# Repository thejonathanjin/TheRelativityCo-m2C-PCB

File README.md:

# m2C: Mobile to Car Communication Module w/ AndroidOS (iOS TBD)

m2C is a capstone project among 4 students from San Jose State University.

The team aimed to achieve connectivity between an Android (and iOS TBD) mobile device and an automobile.

Successfully installed a prototype version in April 2014 in Hayward, Fremont, Milpitas, and San Jose California.

Currently, the lead competitor is Viper SmartStart.

## Installation

Download the latest Diptrace *.dch Schematic and *.dip PCB Layout files.

Tree:

```
.
├── Diptrace
│   └── *.dch
    └── *.dip
```

## Usage

*.dch

```python
```

*.dip

```python
```

KiCAD PCB project from converted DipTrace PCB Layout:

## Contributing

Pull requests are welcome. For major changes, please open an issue first
to discuss what you would like to change.

Please make sure to update tests as appropriate.

A major thanks to:

- Boran "Brian" Peng, Automotive Master Technician
- Shavinda De Silva, Communication Networks, SIM & GPS
- Joseph Nico Tankeh, Embedded Systems, Arduino & C++
- Jonathan Tuan Tran, Android & (iOS TBD)

... for initiating this project!

A big THANK YOU to Dr. David Parent.

## License

Creative Commons

[The Unlicense] (https://choosealicense.com/licenses/unlicense/)

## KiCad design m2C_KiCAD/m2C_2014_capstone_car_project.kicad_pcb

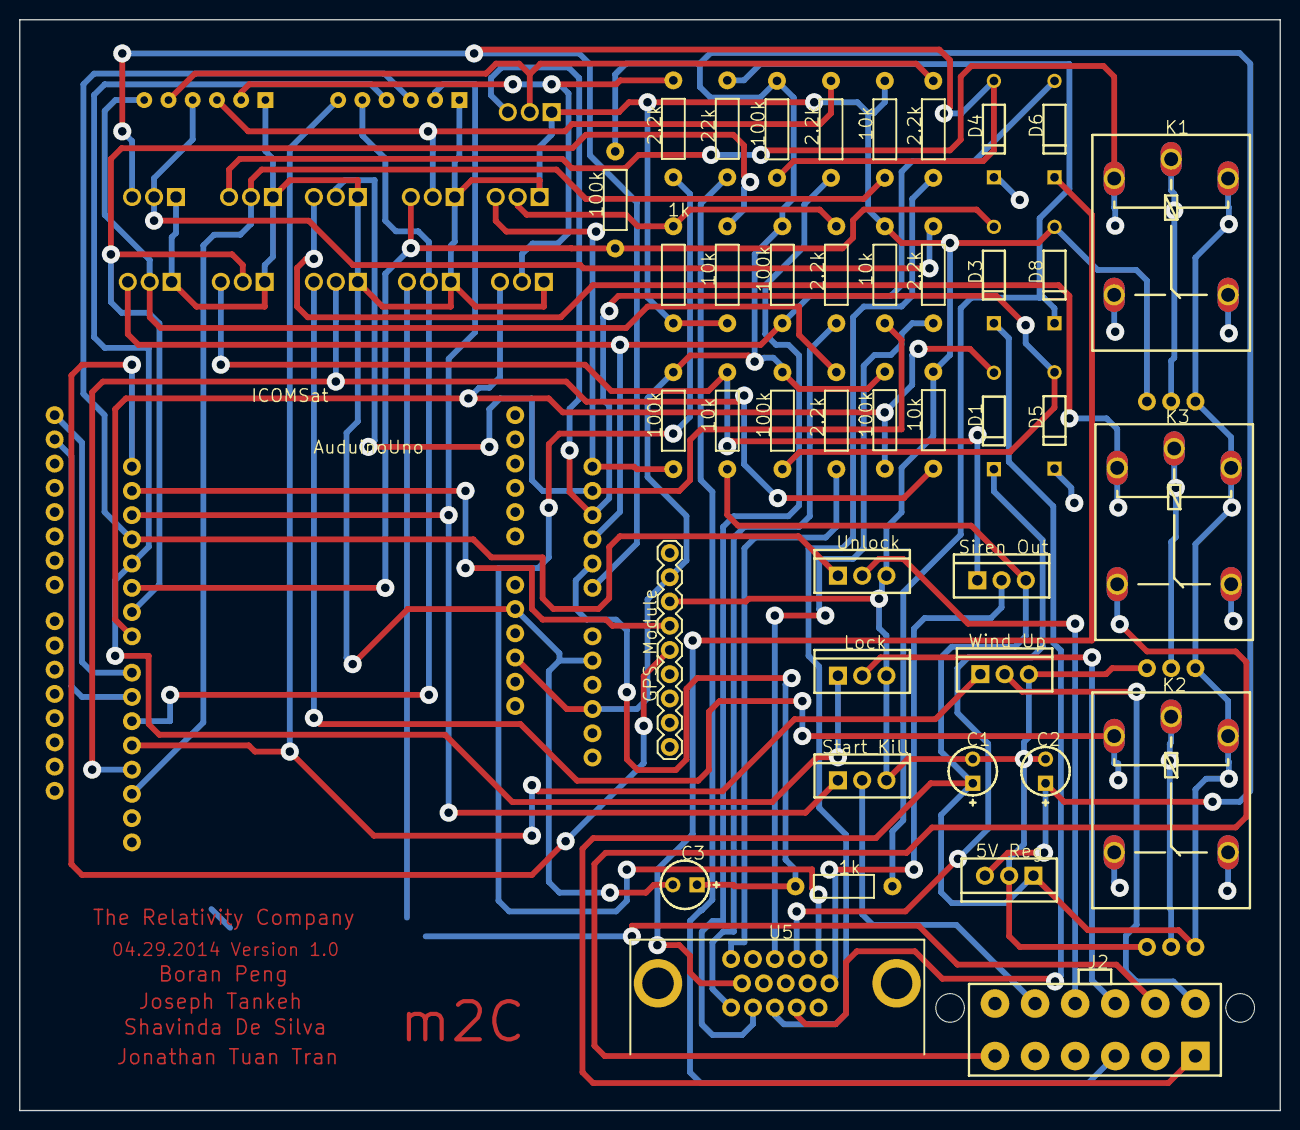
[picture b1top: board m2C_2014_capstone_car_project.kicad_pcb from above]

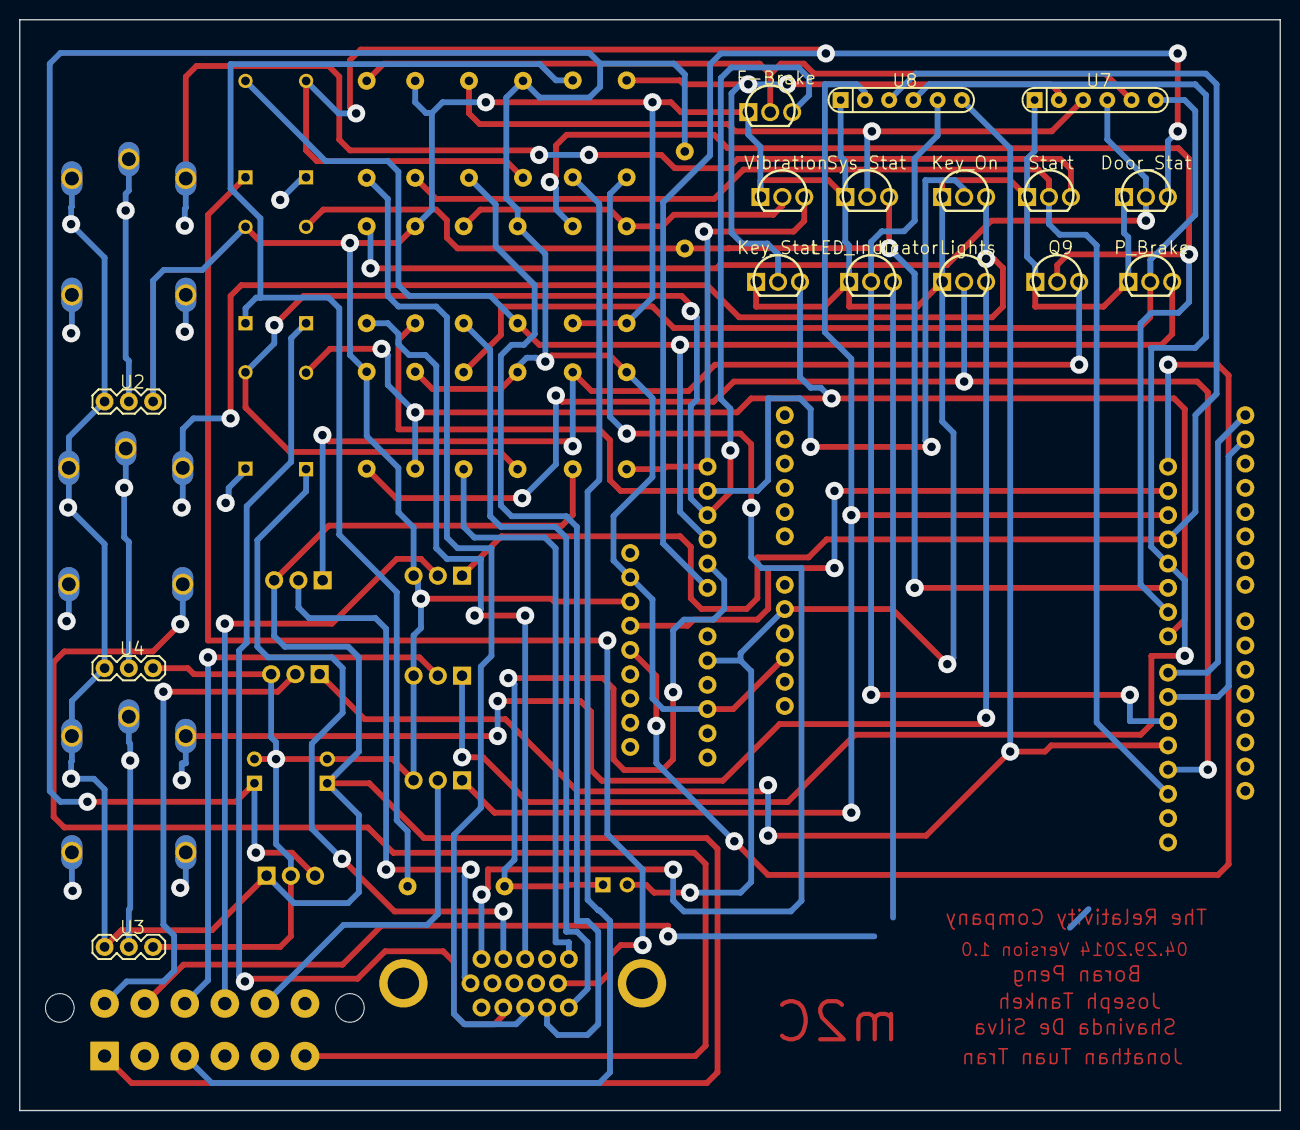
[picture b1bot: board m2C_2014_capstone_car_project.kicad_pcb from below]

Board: 2 copper layers, 132.1 x 114.3 mm, 59 parts (16 on the bottom side), 58 nets.

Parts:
AuduinoUno0: ARDUINO_SHIELDNO_SILK; DUEMILANOVE_VIAS
C1, C2: POLCAP; CAPPR-2.54_5.08
C3: POLCAP; CAPPR-2.54_5.08_C3
D1, D3, D4, D5, D6, D8: 1N4148; DO-35
Door_Stat0: 2N7000_B; TO-92_B
F-Brake0: 2N7000_B; TO-92_B
GPS_Module0: M09; 1X09
ICOMSat0: ARDUINO_SHIELDNO_SILK; DUEMILANOVE_VIAS
J2: 39-29-9123
K1, K2, K3: G5L; G5LE
Key_On0: 2N7000_B; TO-92_B
Key_Stat0: 2N7000_B; TO-92_B
LED_Indicator0: 2N7000_B; TO-92_B
Lights0: 2N7000_B; TO-92_B
Lock0: IRF641; TO-220_Lock
P_Brake0: 2N7000_B; TO-92_B
Q9: 2N7000_B; TO-92_B
R1: 1k; AXIAL-0.4
R3, R4, R5, R6, R7, R10: 100k; AXIAL-0.4_R3
R14: 1k; AXIAL-0.4_R14
R15, R17, R18, R19, R20, R21: 2.2k; AXIAL-0.4_R3
R22, R23, R25, R26, R27: 10k; AXIAL-0.4_R3
R24: 22k; AXIAL-0.4_R3
Siren_Out0: IRF9511; TO-220_Lock
Start0: 2N7000_B; TO-92_B
Start_Kill0: IRF641; TO-220_Lock
Sys_Stat0: 2N7000_B; TO-92_B
U2, U3, U4: JUMPER-3-OLDPTH; 1X03
U5: DB15
U7: 1k; RPACK-SIP-PTH-5
U8: 10k; RPACK-SIP-PTH-5
UNK5V_Reg0: MC7805ACT; TO-220
Unlock0: IRF641; TO-220_Lock
Vibration0: 2N7000_B; TO-92_B
Wind_Up0: IRF641; TO-220_Lock

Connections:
Net_0: AuduinoUno0.GND@1, C1.2, C2.2, C3.2, D8.2, Door_Stat0.1, F-Brake0.1, GPS_Module0.7, ICOMSat0.GND@1, J2.2, Key_On0.1, Key_Stat0.1, LED_Indicator0.1, Lights0.1, Lock0.3, P_Brake0.1, Q9.1, R14.P$1, R23.P$1, R25.P$2, R26.P$2, R27.P$2, Start0.1, Start_Kill0.3, Sys_Stat0.1, U2.1, U3.1, U4.1, U7.P$1, U8.P$1, UNK5V_Reg0.2, Unlock0.3, Vibration0.1, Wind_Up0.3
Net_1: AuduinoUno0.5V, C2.1, GPS_Module0.8, ICOMSat0.5V, R3.P$2, R4.P$2, R5.P$2, R6.P$2, R7.P$2, R10.P$2, UNK5V_Reg0.3
Net_2: R15.P$1, U5.1
Net_3: D1.1, U5.2
Net_4: R18.P$1, U5.3
Net_5: R20.P$1, U5.5
Net_6: AuduinoUno0.D6, Q9.2, R23.P$2
Net_7: C1.1, J2.1, K1.2, K2.2, K3.2, R22.P$1, Siren_Out0.3, U2.3, U3.3, U4.3, UNK5V_Reg0.1
Net_8: Siren_Out0.2, U5.6
Net_9: D4.1, U5.8
Net_10: D5.1, U5.9
Net_11: D6.1, U5.10
Net_12: D3.1, U5.12
Net_13: R19.P$1, U5.13
Net_14: R17.P$1, U5.14
Net_15: R21.P$1, U5.15
Net_16: J2.10, Unlock0.2
Net_17: AuduinoUno0.D11, U8.P$6, Wind_Up0.1
Net_18: J2.3, R24.P$1
Net_19: K2.P, U3.2
Net_20: AuduinoUno0.A4, Key_On0.2, R25.P$1
Net_21: AuduinoUno0.D13, R27.P$1, Start0.2
Net_22: AuduinoUno0.D12, Lights0.2, R26.P$1
Net_23: K2.1, Lights0.3
Net_24: K3.1, Key_On0.3
Net_25: K1.1, Start0.3
Net_26: F-Brake0.2, R19.P$2, U7.P$5
Net_27: P_Brake0.2, R20.P$2, U7.P$6
Net_28: R14.P$2, R21.P$2, Vibration0.2
Net_29: AuduinoUno0.A3, D5.2, F-Brake0.3, R5.P$1
Net_30: AuduinoUno0.A2, D6.2, P_Brake0.3, R6.P$1
Net_31: AuduinoUno0.A5, R7.P$1, Vibration0.3
Net_32: AuduinoUno0.A0, D4.2, Door_Stat0.3, R4.P$1
Net_33: AuduinoUno0.D5, D3.2, R3.P$1, Sys_Stat0.3
Net_34: R17.P$2, Sys_Stat0.2, U7.P$3
Net_36: AuduinoUno0.D7, D1.2, Key_Stat0.3, R10.P$1
Net_37: Key_Stat0.2, R15.P$2, U7.P$2
Net_38: Q9.3, R22.P$2, Siren_Out0.1
Net_39: D8.1, R1.P$1, R24.P$2
Net_40: K1.P, U2.2
Net_41: K3.P, U4.2
Net_42: J2.4, K1.S
Net_43: J2.5, K2.S
Net_44: J2.6, K3.S
Net_45: AuduinoUno0.D10, LED_Indicator0.2, U8.P$5
Net_46: J2.11, Start_Kill0.2
Net_47: J2.9, Lock0.2
Net_48: AuduinoUno0.D4, Lock0.1, U8.P$4
Net_49: AuduinoUno0.D3, U8.P$3, Unlock0.1
Net_50: AuduinoUno0.D2, Start_Kill0.1, U8.P$2
Net_51: AuduinoUno0.D8, ICOMSat0.RX
Net_53: J2.8, LED_Indicator0.3
Net_54: J2.7, Wind_Up0.2
Net_56: AuduinoUno0.TX, GPS_Module0.6
Net_57: AuduinoUno0.A1, C3.1, R1.P$2
Net_61: Door_Stat0.2, R18.P$2, U7.P$4
Net_62: AuduinoUno0.D9, ICOMSat0.TX
Net_63: AuduinoUno0.RX, GPS_Module0.5
